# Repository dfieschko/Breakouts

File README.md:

# Breakouts
 A repository for KiCAD files describing breakout boards for a variety of chips and circuits. Each subfolder has its own readme to describe what the board does.

 I have written Arduino libraries for several of these boards - they should be linked in the READMEs for the relevant projects.

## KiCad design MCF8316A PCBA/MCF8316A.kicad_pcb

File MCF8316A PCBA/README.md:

# MCF8316A
This one isn't a breakout board so much as just a mini motor controller board integrating TI's MCF8316A codeless motor controller IC along with some switches and a rotary potentiometer for adjusting speed.

Feel free to use it however you wish.

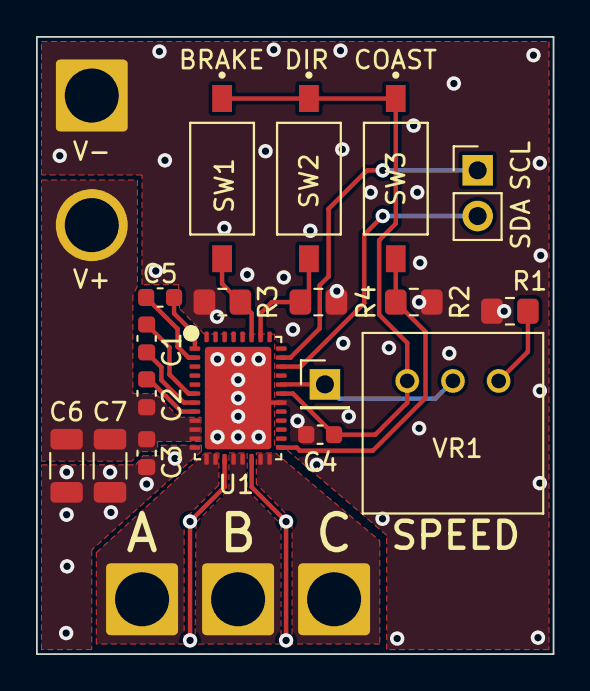
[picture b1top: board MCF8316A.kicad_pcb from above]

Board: 2 copper layers, 28.7 x 34.3 mm, 22 parts (0 on the bottom side), 18 nets.

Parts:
C1: 47n; C_0603_1608Metric
C2, C3, C4, C5: 1u; C_0603_1608Metric
C6, C7: 10u; C_1206_3216Metric
J1, J2, J3: 12AWG; SolderWire-2.5sqmm_1x01_D2.4mm_OD3.6mm
J4: Header_0.254mm; PinHeader_1x02_P2.54mm_Vertical
J5: Wire; PinHeader_1x01_P2.54mm_Vertical
J6: 12AWG; SolderWire-2.5sqmm_1x02_P7.2mm_D2.4mm_OD3.6mm
R1: 300-800; R_0805_2012Metric_Pad1.20x1.40mm_HandSolder
R2, R3, R4: 10k; R_0805_2012Metric_Pad1.20x1.40mm_HandSolder
SW1, SW2, SW3: DIP_SMC; SW_DS04-254-1-01BK-SMT
U1: MCF8316A
VR1: 3310R-125-103L

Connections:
+3V3: C4.1, SW1.1, SW2.1, SW3.1, U1.27 (AVDD), VR1.3
/A: J1.1, U1.13 (OUTA), U1.14 (OUTA)
/B: J2.1, U1.16 (OUTB), U1.17 (OUTB)
/BRAKE: R3.1, SW1.2, U1.35 (BRAKE)
/C: J3.1, U1.19 (OUTC), U1.20 (OUTC)
/COAST: R2.1, SW3.2, U1.21 (DRVOFF)
/CP: C2.2, U1.8 (CP)
/CPH: C1.1, U1.7 (CPH)
/CPL: C1.2, U1.6 (CPL)
/DGND: C5.1, U1.2 (DGND)
/DIRECTION: R4.1, SW2.2, U1.34 (DIR)
/DVDD: C5.2, U1.1 (DVDD)
/SCL: J4.1, U1.31 (SCL)
/SDA: J4.2, U1.30 (SDA)
/SPEED: J5.1, U1.28 (SPEED/WAKE), VR1.2
GND: C3.2, C4.2, C6.2, C7.2, J6.1, R1.1, R2.2, R3.2, R4.2, U1.0 (GNDPAD), U1.12 (PGND), U1.15 (PGND), U1.18 (PGND), U1.26 (AGND)
unnamed: R1.2, VR1.1
VDD: C2.1, C3.1, C6.1, C7.1, J6.2, U1.9 (VM), U1.10 (VM), U1.11 (VM)

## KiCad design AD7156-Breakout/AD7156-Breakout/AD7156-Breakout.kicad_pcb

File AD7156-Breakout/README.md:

# AD7156-Breakout

KiCAD files for AD7156 breakout boards.

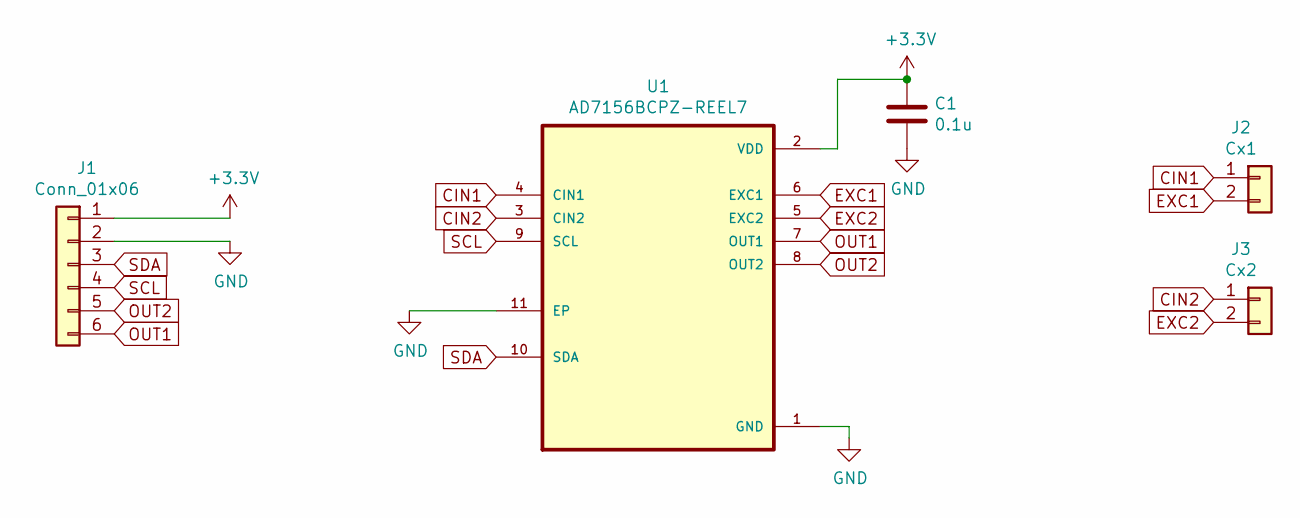
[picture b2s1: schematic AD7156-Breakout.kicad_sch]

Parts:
C1: 0.1u; C_0603_1608Metric
J1: Conn_01x06; PinSocket_1x06_P2.54mm_Vertical
J2: Cx1; PinSocket_1x02_P2.54mm_Vertical
J3: Cx2; PinSocket_1x02_P2.54mm_Vertical
U1: AD7156BCPZ-REEL7; SON50P300X300X80-11N

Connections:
+3V3: C1.1, J1.1, U1.2 (VDD)
CIN1: J2.1, U1.4 (CIN1)
CIN2: J3.1, U1.3 (CIN2)
EXC1: J2.2, U1.6 (EXC1)
EXC2: J3.2, U1.5 (EXC2)
GND: C1.2, J1.2, U1.1 (GND), U1.11 (EP)
OUT1: J1.6, U1.7 (OUT1)
OUT2: J1.5, U1.8 (OUT2)
SCL: J1.4, U1.9 (SCL)
SDA: J1.3, U1.10 (SDA)

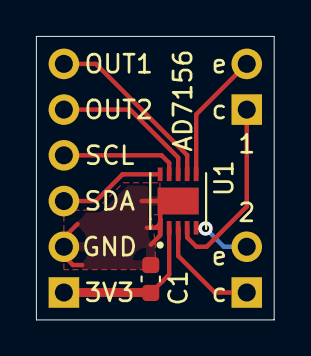
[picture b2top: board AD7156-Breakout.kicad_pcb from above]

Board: 2 copper layers, 13.2 x 15.7 mm, 5 parts (1 on the bottom side), 10 nets.

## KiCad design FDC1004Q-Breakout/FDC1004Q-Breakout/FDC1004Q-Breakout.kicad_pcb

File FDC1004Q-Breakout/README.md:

# FDC1004Q-Breakout
KiCAD files for breakout boards for TI's FDC1004Q Capacitance-to-Digital converters. To my knowledge, these work identically to the FDC1004, so if that's what you're prototyping for these boards should still work fine.

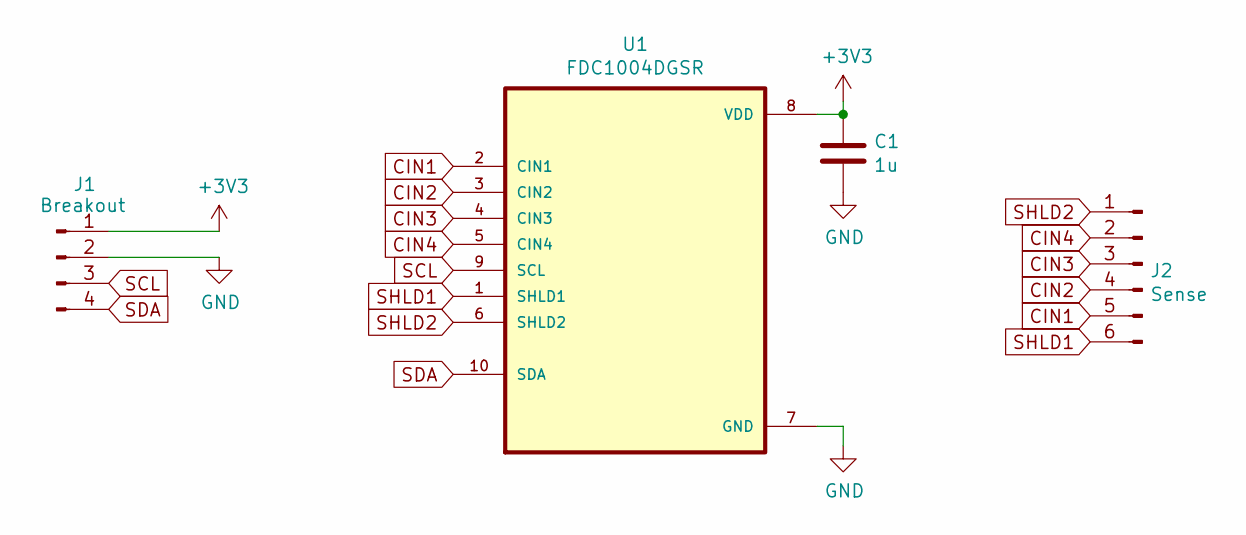
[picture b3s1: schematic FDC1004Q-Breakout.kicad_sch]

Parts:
C1: 1u; C_0603_1608Metric
J1: Breakout; PinHeader_1x04_P2.54mm_Vertical
J2: Sense; PinHeader_1x06_P2.00mm_Vertical
U1: FDC1004DGSR; SOP50P490X110-10N

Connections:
+3V3: C1.1, J1.1, U1.8 (VDD)
CIN1: J2.5, U1.2 (CIN1)
CIN2: J2.4, U1.3 (CIN2)
CIN3: J2.3, U1.4 (CIN3)
CIN4: J2.2, U1.5 (CIN4)
GND: C1.2, J1.2, U1.7 (GND)
SCL: J1.3, U1.9 (SCL)
SDA: J1.4, U1.10 (SDA)
SHLD1: J2.6, U1.1 (SHLD1)
SHLD2: J2.1, U1.6 (SHLD2)

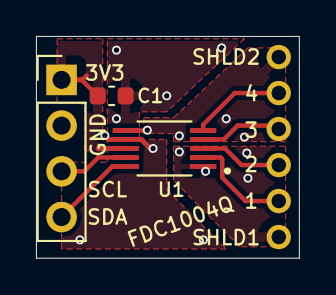
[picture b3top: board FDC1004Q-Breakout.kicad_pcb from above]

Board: 2 copper layers, 14.6 x 12.3 mm, 4 parts (0 on the bottom side), 10 nets.

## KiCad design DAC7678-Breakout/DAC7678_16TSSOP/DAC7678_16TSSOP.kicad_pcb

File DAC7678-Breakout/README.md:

# DAC7678-Breakout
KiCAD files for breakout boards for TI's DAC7678 I2C-controlled digital-to-analog converters.

There are currently only files for the TSSOP-16 footprint chips. Files for the 24VQFN chips may be forthcoming.

This design was created only recently and hasn't even been realized physically, let alone tested! Test results will be added somewhere in the repository once they're ready.

I am also in the process of writing an Arduino library for communicating with the DAC7678, which can be found here: https://github.com/dfieschko/DAC7678-Arduino.

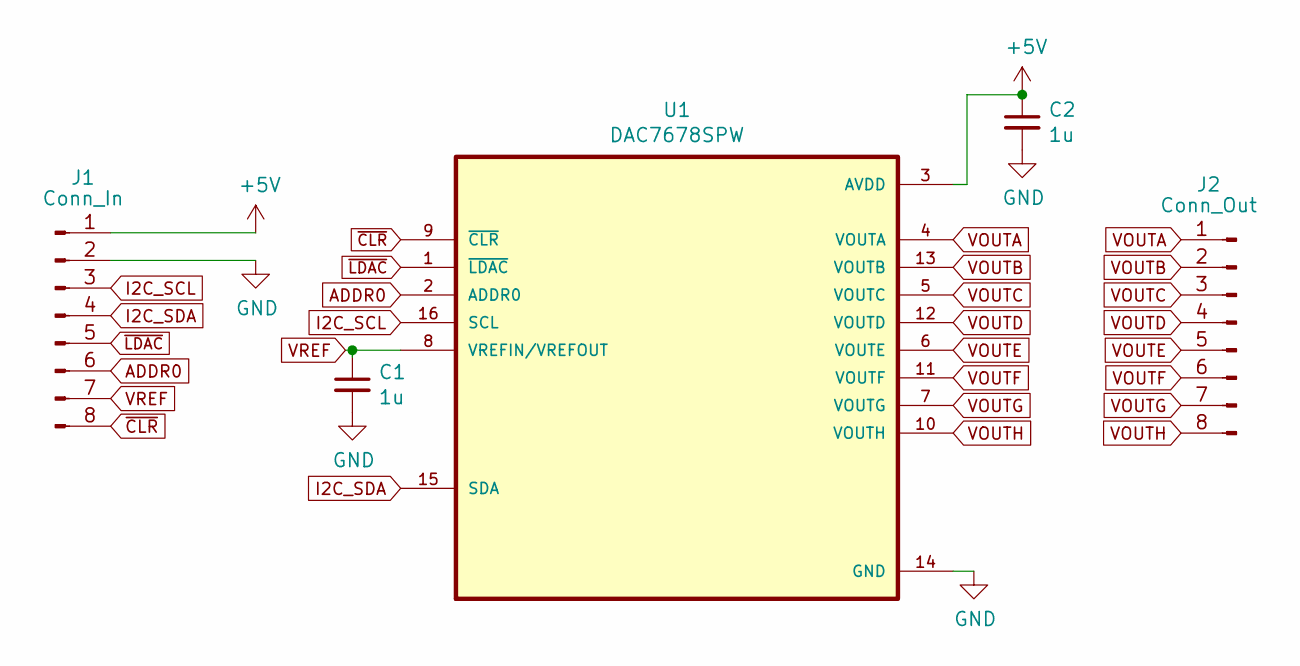
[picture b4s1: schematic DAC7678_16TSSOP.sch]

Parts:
C1, C2: 1u; C_0603_1608Metric
J1: Conn_In; PinSocket_1x08_P2.54mm_Vertical
J2: Conn_Out; PinSocket_1x08_P2.54mm_Vertical
U1: DAC7678SPW; SOP65P640X120-16N

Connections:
+5V: C2.1, J1.1, U1.3 (AVDD)
ADDR0: J1.6, U1.2 (ADDR0)
GND: C1.2, C2.2, J1.2, U1.14 (GND)
I2C_SCL: J1.3, U1.16 (SCL)
I2C_SDA: J1.4, U1.15 (SDA)
VOUTA: J2.1, U1.4 (VOUTA)
VOUTB: J2.2, U1.13 (VOUTB)
VOUTC: J2.3, U1.5 (VOUTC)
VOUTD: J2.4, U1.12 (VOUTD)
VOUTE: J2.5, U1.6 (VOUTE)
VOUTF: J2.6, U1.11 (VOUTF)
VOUTG: J2.7, U1.7 (VOUTG)
VOUTH: J2.8, U1.10 (VOUTH)
VREF: C1.1, J1.7, U1.8 (VREFIN/VREFOUT)
~CLR: J1.8, U1.9 (~CLR)
~LDAC: J1.5, U1.1 (~LDAC)

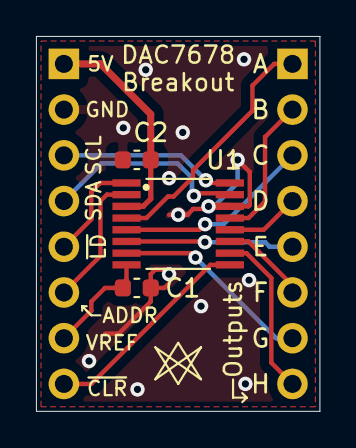
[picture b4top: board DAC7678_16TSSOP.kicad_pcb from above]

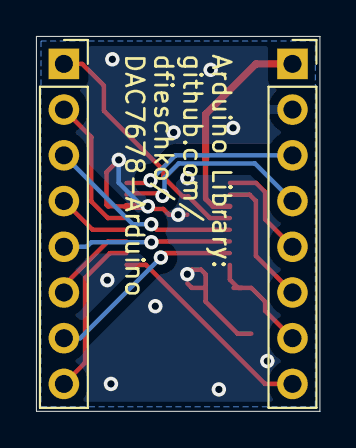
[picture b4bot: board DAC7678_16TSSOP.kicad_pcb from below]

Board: 2 copper layers, 15.7 x 20.8 mm, 5 parts (2 on the bottom side), 16 nets.

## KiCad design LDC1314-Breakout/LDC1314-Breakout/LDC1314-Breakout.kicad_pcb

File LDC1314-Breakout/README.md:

# LDC1314-Breakout
KiCAD files for breakout boards for TI's LDC1314 inductance-to-digital converter chips.

This design was created only recently and hasn't even been realized physically, let alone tested! Test results will be added somewhere in the repository once they're ready.

I also wrote Teensy libraries for this chip, which can be ported to other Arduino boards without much hassle. I intend to port the libraries to all Arduino boards in the near future. I also intend to write more thorough instructions and documentation, as well as a quick-start guide.
The libraries can be found here: https://github.com/dfieschko/LDC1312-Arduino

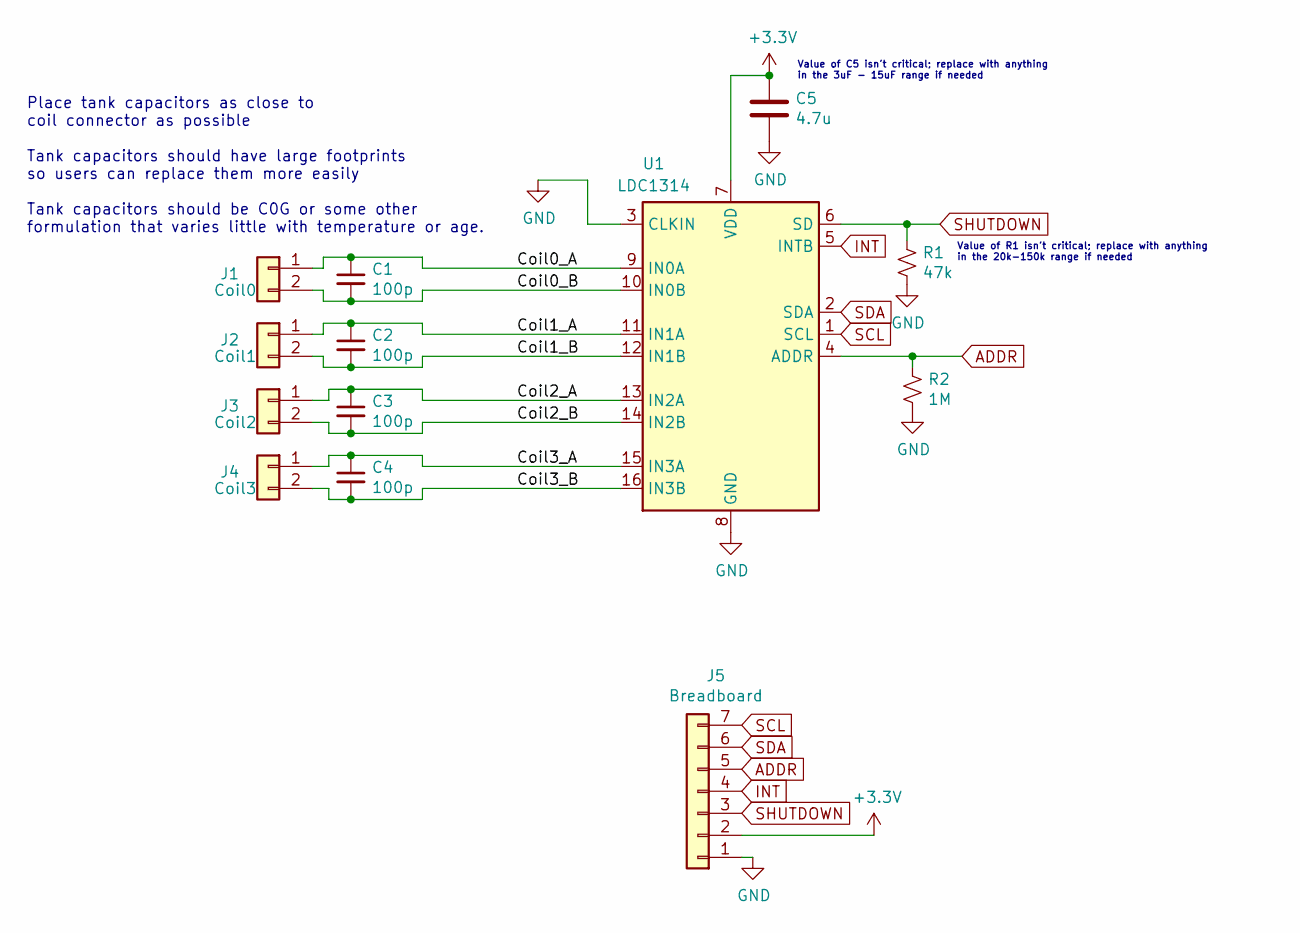
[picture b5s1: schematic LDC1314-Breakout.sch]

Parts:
C1, C2, C3, C4: 100p; C_0805_2012Metric_Pad1.18x1.45mm_HandSolder
C5: 4.7u; C_0603_1608Metric
J1: Coil0; PinHeader_1x02_P1.27mm_Vertical
J2: Coil1; PinHeader_1x02_P1.27mm_Vertical
J3: Coil2; PinHeader_1x02_P1.27mm_Vertical
J4: Coil3; PinHeader_1x02_P1.27mm_Vertical
J5: Breadboard; PinHeader_1x07_P2.54mm_Vertical
R1: 47k; R_0603_1608Metric
R2: 1M; R_0603_1608Metric
U1: LDC1314; WQFN-16-1EP_4x4mm_P0.5mm_EP2.6x2.6mm_ThermalVias

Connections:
+3V3: C5.1, J5.2, U1.7 (VDD)
/Coil0_A: C1.1, J1.1, U1.9 (IN0A)
/Coil0_B: C1.2, J1.2, U1.10 (IN0B)
/Coil1_A: C2.1, J2.1, U1.11 (IN1A)
/Coil1_B: C2.2, J2.2, U1.12 (IN1B)
/Coil2_A: C3.1, J3.1, U1.13 (IN2A)
/Coil2_B: C3.2, J3.2, U1.14 (IN2B)
/Coil3_A: C4.1, J4.1, U1.15 (IN3A)
/Coil3_B: C4.2, J4.2, U1.16 (IN3B)
ADDR: J5.5, R2.1, U1.4 (ADDR)
GND: C5.2, J5.1, R1.2, R2.2, U1.3 (CLKIN), U1.8 (GND), U1.17 (GND)
INT: J5.4, U1.5 (INTB)
SCL: J5.7, U1.1 (SCL)
SDA: J5.6, U1.2 (SDA)
SHUTDOWN: J5.3, R1.1, U1.6 (SD)

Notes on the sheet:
Place tank capacitors as close to coil connector as possible Tank capacitors should have large footprints so users can replace them more easily Tank capacitors should be C0G or some other formulation that varies little with temperature or age.
Value of R1 isn't critical; replace with anything in the 20k-150k range if needed
Value of C5 isn't critical; replace with anything in the 3uF - 15uF range if needed

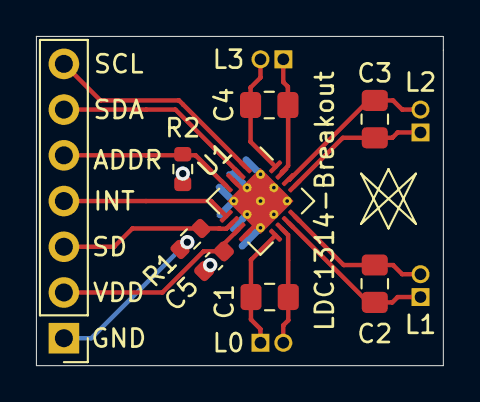
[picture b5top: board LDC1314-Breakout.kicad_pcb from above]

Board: 2 copper layers, 22.6 x 18.3 mm, 13 parts (0 on the bottom side), 15 nets.

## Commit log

2021-11-19 Add Arduino library URL to DAC7678 silkscreen
2022-01-12 Push update
2022-02-02 Update AD7156
2022-02-03 Minor updates to AD7156, FDC1004Q
2022-02-06 Add MCF8316A PCB

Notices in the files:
parts and their libraries:
Copyright 2021 Accelerated Designs. All rights reserved.
